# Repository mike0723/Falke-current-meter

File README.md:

A current (and voltage) meter to keep track of the battery state at out off grid RC airstrip.

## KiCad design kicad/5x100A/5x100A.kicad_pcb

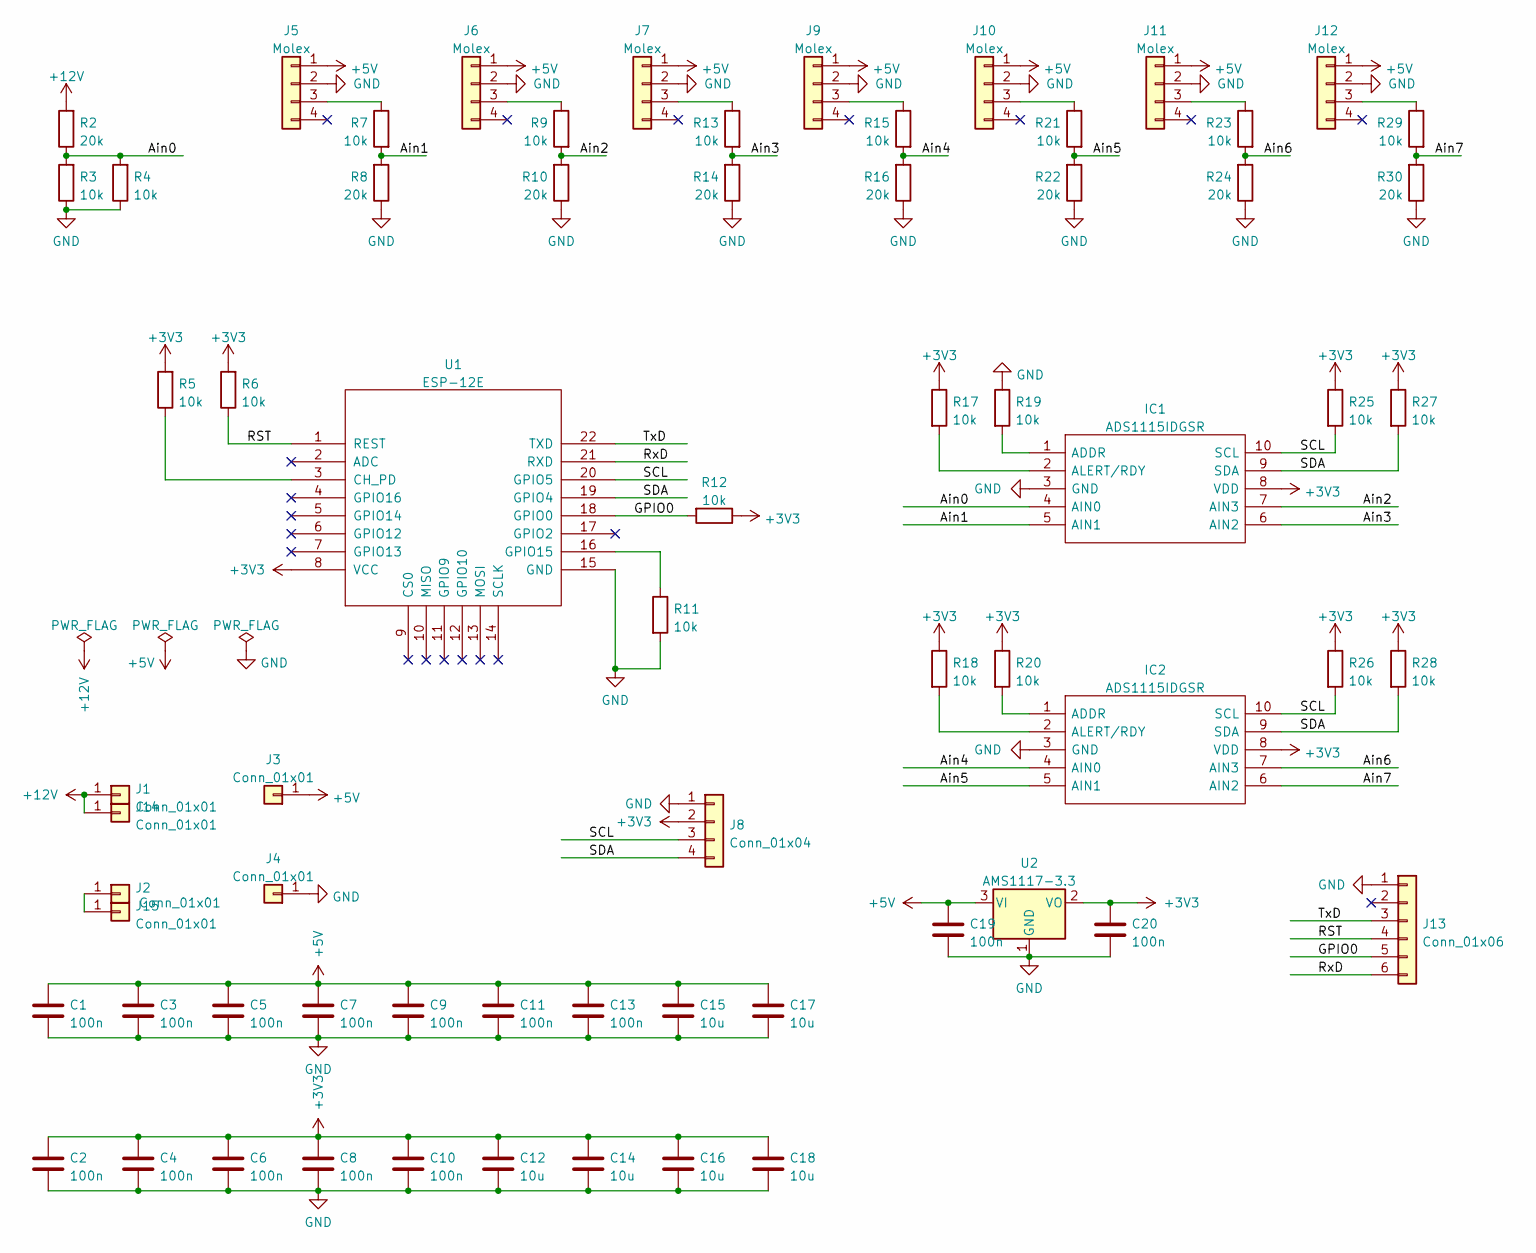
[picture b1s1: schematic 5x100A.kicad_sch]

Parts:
C1, C2, C3, C4, C5, C6, C7, C8, C9, C10, C11, C13, C19, C20: 100n; C_0805_2012Metric
C12, C14, C15, C16, C17, C18: 10u; C_1206_3216Metric
IC1, IC2: ADS1115IDGSR; VSSOP-10_3x3mm_P0.5mm; Manufacturer_Part_Number ADS1115IDGSR; Mouser Part Number 595-ADS1115IDGSR
J1, J2, J3, J4, J14, J15: Conn_01x01; PinHeader_1x01_P2.54mm_Vertical
J5, J6, J7, J9, J10, J11, J12: Molex; Molex_KK-254_AE-6410-04A_1x04_P2.54mm_Vertical
J8: Conn_01x04; PinHeader_1x04_P2.54mm_Vertical
J13: Conn_01x06; PinHeader_1x06_P2.54mm_Vertical
R2, R8, R10, R14, R16, R22, R24, R30: 20k; R_0805_2012Metric
R3, R4, R5, R6, R7, R9, R11, R12, R13, R15, R17, R18, R19, R20, R21, R23, R25, R26, R27, R28, R29: 10k; R_0805_2012Metric
U1: ESP-12E
U2: AMS1117-3.3; SOT-223-3_TabPin2

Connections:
+3V3: C2.1, C4.1, C6.1, C8.1, C10.1, C12.1, C14.1, C16.1, C18.1, C20.1, IC1.8 (VDD), IC2.8 (VDD), J8.2, R5.2, R6.2, R12.1, R17.1, R18.1, R20.1, R25.1, R26.1, R27.1, R28.1, U1.8 (VCC), U2.2 (VO)
+5V: C1.1, C3.1, C5.1, C7.1, C9.1, C11.1, C13.1, C15.1, C17.1, C19.1, J3.1, J5.1, J6.1, J7.1, J9.1, J10.1, J11.1, J12.1, U2.3 (VI)
+12V: J1.1, J14.1, R2.2
/Ain0: IC1.4 (AIN0), R2.1, R3.2, R4.2
/Ain1: IC1.5 (AIN1), R7.2, R8.2
/Ain2: IC1.7 (AIN3), R9.2, R10.2
/Ain3: IC1.6 (AIN2), R13.2, R14.2
/Ain4: IC2.4 (AIN0), R15.2, R16.2
/Ain5: IC2.5 (AIN1), R21.2, R22.2
/Ain6: IC2.7 (AIN3), R23.2, R24.2
/Ain7: IC2.6 (AIN2), R29.2, R30.2
/GPIO0: J13.5, R12.2, U1.18 (GPIO0)
/RST: J13.4, R6.1, U1.1 (REST)
/RxD: J13.6, U1.21 (RXD)
/SCL: IC1.10 (SCL), IC2.10 (SCL), J8.3, R25.2, R26.2, U1.20 (GPIO5)
/SDA: IC1.9 (SDA), IC2.9 (SDA), J8.4, R27.2, R28.2, U1.19 (GPIO4)
/TxD: J13.3, U1.22 (TXD)
GND: C1.2, C2.2, C3.2, C4.2, C5.2, C6.2, C7.2, C8.2, C9.2, C10.2, C11.2, C12.2, C13.2, C14.2, C15.2, C16.2, C17.2, C18.2, C19.2, C20.2, IC1.3 (GND), IC2.3 (GND), J4.1, J5.2, J6.2, J7.2, J8.1, J9.2, J10.2, J11.2, J12.2, J13.1, R3.1, R4.1, R8.1, R10.1, R11.2, R14.1, R16.1, R19.1, R22.1, R24.1, R30.1, U1.15 (GND), U2.1 (GND)
unnamed: IC1.1 (ADDR), R19.2
unnamed: IC1.2 (ALERT/RDY), R17.2
unnamed: IC2.1 (ADDR), R20.2
unnamed: IC2.2 (ALERT/RDY), R18.2
unnamed: J5.3, R7.1
unnamed: J6.3, R9.1
unnamed: J7.3, R13.1
unnamed: J9.3, R15.1
unnamed: J10.3, R21.1
unnamed: J11.3, R23.1
unnamed: J12.3, R29.1
unnamed: J2.1, J15.1
unnamed: R5.1, U1.3 (CH_PD)
unnamed: R11.1, U1.16 (GPIO15)

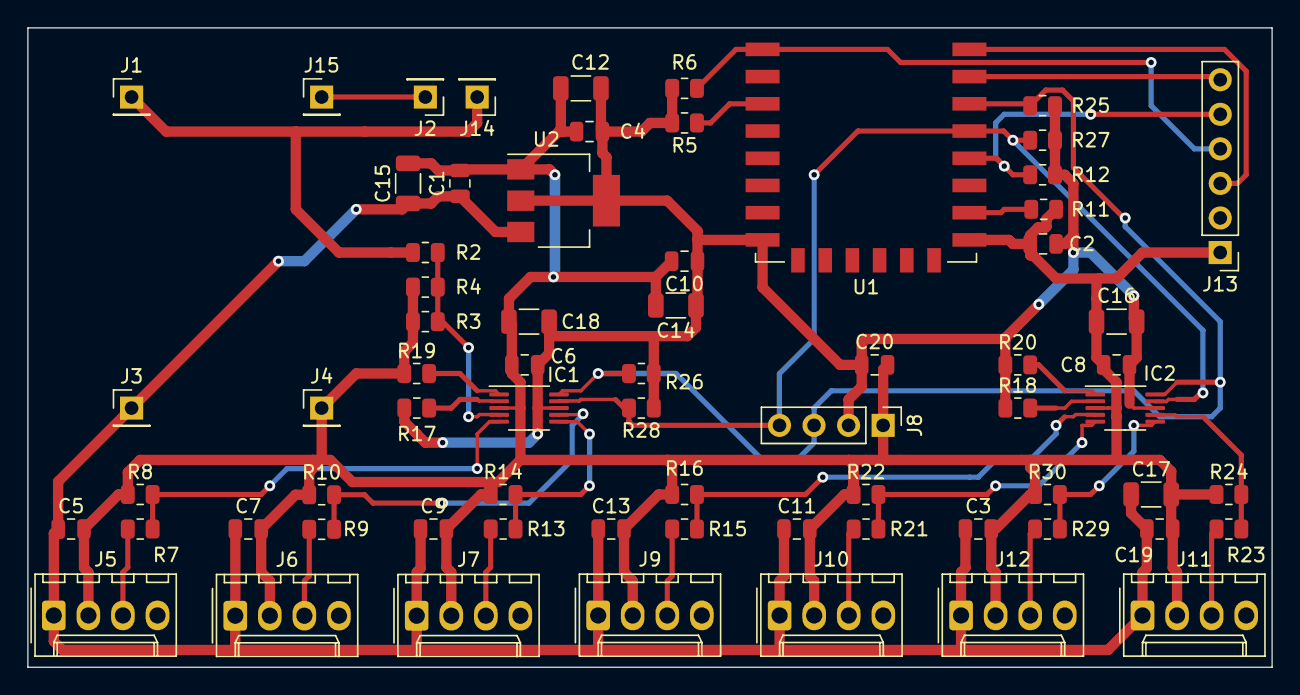
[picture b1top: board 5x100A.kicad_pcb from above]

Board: 2 copper layers, 91.4 x 47.0 mm, 68 parts (0 on the bottom side), 32 nets.
